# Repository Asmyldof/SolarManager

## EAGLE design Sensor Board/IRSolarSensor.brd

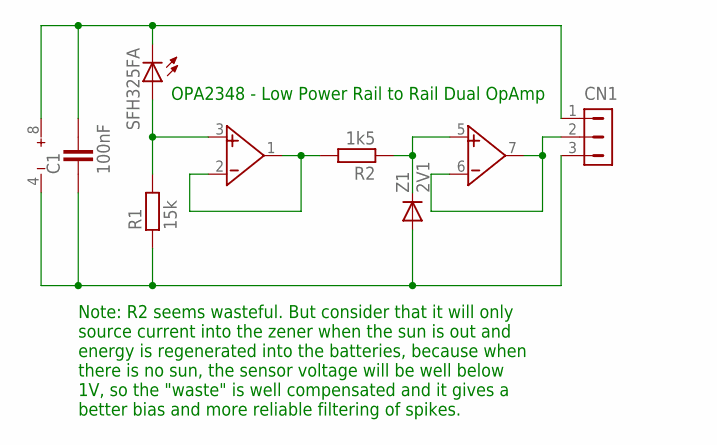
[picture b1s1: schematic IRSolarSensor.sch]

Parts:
C1: 100nF; CAPC1608X92N
CN1: HDR-1X3-MTA-100; MTA-100-3V
R1: 15k; RESC2012X70N
R2: 1k5; RESC1608X55N
SFH325FA: LEDSIDELED; OSRAM-SIDELED
U$1: OPA2348; DCN-R-PDSO-G8
Z1: 2V1; MINIMELF

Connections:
BUFFER: R2.2, U$1.1 (O), U$1.2 (-)
GND: C1.1, CN1.3, R1.1, U$1.4 (V-), Z1.A
unnamed: R2.1, U$1.5 (+), Z1.C
OUT: CN1.2, U$1.6 (-), U$1.7 (O)
SENSOR: R1.2, SFH325FA.A, U$1.3 (+)
VCC: C1.2, CN1.1, SFH325FA.C, U$1.8 (V+)

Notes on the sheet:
OPA2348 - Low Power Rail to Rail Dual OpAmp
Note: R2 seems wasteful. But consider that it will only source current into the zener when the sun is out and energy is regenerated into the batteries, because when there is no sun, the sensor voltage will be well below 1V, so the "waste" is well compensated and it gives a better bias and more reli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

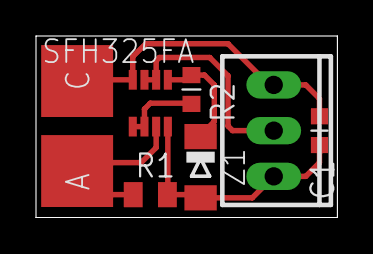
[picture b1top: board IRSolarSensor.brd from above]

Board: 2 copper layers, 16.7 x 10.1 mm, 7 parts (0 on the bottom side), 6 nets.

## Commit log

2014-11-06 Initial program creation: Atmel ATTiny10 Solar Harvester and Light Monitor
2014-11-09 Working through the defines, adding some basic code
2014-11-09 Some more tiny changes before bedtime
2014-11-10 Fully completed code, commit before read-through to check compatibility with algorithm
2014-11-10 Added a full description, copyright and notice to the top of the code
2014-11-10 Forgot to add the ticks recalculation when entering night-mode. Fixed.
2014-11-10 Added Sensor Board design files
2014-11-10 Added minimum daylength to prevent light effects continuously retriggering.
2014-11-10 Final version for production before install.
2014-11-10 Few small changes and possibly fixed the night install. Bed time now (first in 36hours).
2014-11-10 Tested un-inline-ing helper functions, increased code size, so took out the note.
2014-11-11 Added dutch description of original project and checked some variables
2014-11-11 Added "written by" to dutch project description
2014-11-11 Added some photos to the documentation
2014-11-12 Added note in the description of sleep mode about PWM and power down. Also new Preprocessor TODO.
2014-12-18 Separated the definitions from the code, to fascilitate the needed changes
2014-12-18 Added differentiation between Day and Night in ticks, for more flexibility in factor
2014-12-18 Added: - Dimming settings after two independant intervals; - Resetting of DayStreak only after a certain amount of night-activity
2014-12-19 Added a calibration project, to calibrate the prescaling to the actual WDC frequency. Started debugging the new day/night system.
2014-12-19 Added brackets to all formulaic defines, in hopes to fix some operational bugs that may be caused by recursive defines.
2014-12-19 Some small modifications to configuration definitions
2014-12-19 Reverted all configurations to "public defaults"

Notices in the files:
parts and their libraries:
con-hdrs40: Copyright (C) 2004, Bob Starr (bobstarr@mindspring.com)
